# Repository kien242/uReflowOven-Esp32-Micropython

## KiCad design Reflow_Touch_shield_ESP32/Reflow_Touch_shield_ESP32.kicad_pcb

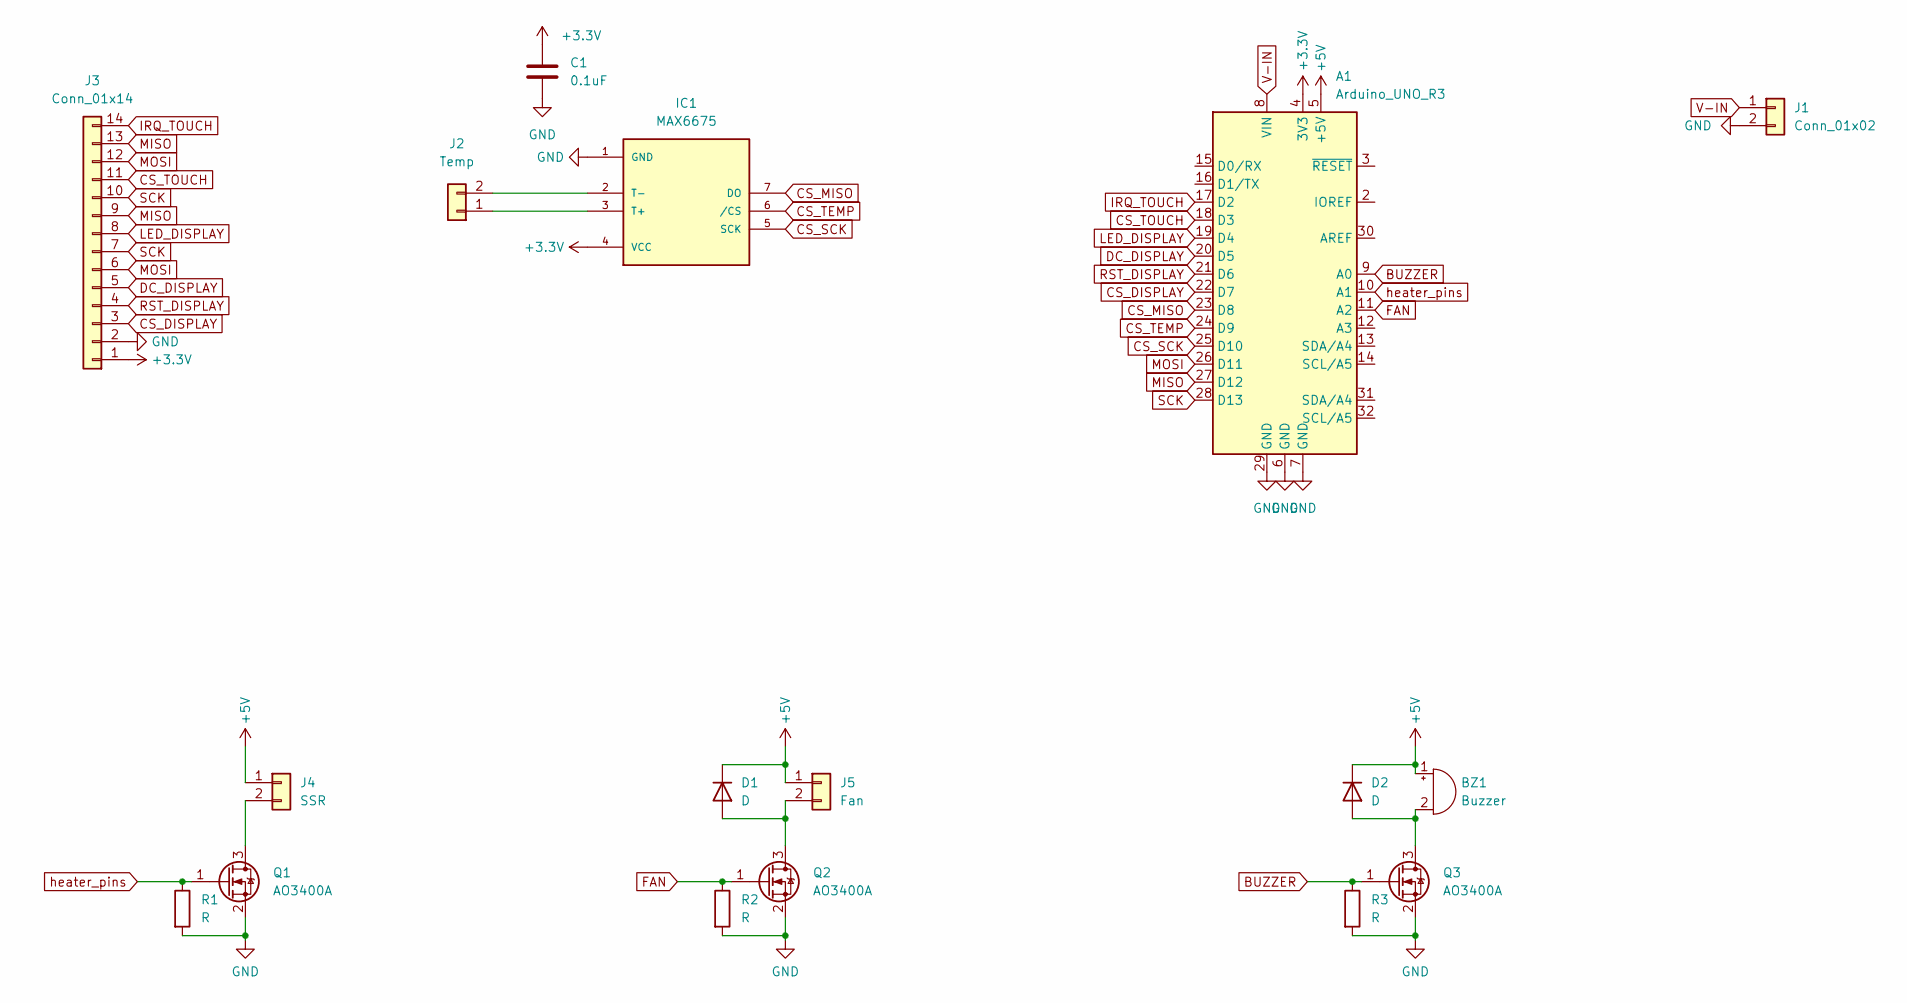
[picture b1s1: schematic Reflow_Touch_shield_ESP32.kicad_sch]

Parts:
A1: Arduino_UNO_R3
BZ1: Buzzer; MagneticBuzzer_CUI_CMT-8504-100-SMT
C1: 0.1uF; C_0603_1608Metric_Pad1.08x0.95mm_HandSolder
D1, D2: D; D_SOD-123
IC1: MAX6675; SO08
J1: Conn_01x02; TerminalBlock_Phoenix_MKDS-1,5-2-5.08_1x02_P5.08mm_Horizont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
J2: Temp; JST_EH_S2B-EH_1x02_P2.50mm_Horizontal
J3: Conn_01x14; ILI9341_PCB
J4: SSR; JST_EH_S2B-EH_1x02_P2.50mm_Horizontal
J5: Fan; JST_EH_S2B-EH_1x02_P2.50mm_Horizontal
Q1, Q2, Q3: AO3400A; SOT-23_Handsoldering
R1, R2, R3: R; R_0603_1608Metric_Pad0.98x0.95mm_HandSolder

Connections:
+3.3V: A1.4 (3V3), C1.1, IC1.4 (VCC), J3.1
+5V: A1.5 (+5V), BZ1.1 (-), D1.1 (K), D2.1 (K), J4.1, J5.1
BUZZER: A1.9 (A0), Q3.1 (G), R3.1
CS_DISPLAY: A1.22 (D7), J3.3
CS_MISO: A1.23 (D8), IC1.7 (DO)
CS_SCK: A1.25 (D10), IC1.5 (SCK)
CS_TEMP: A1.24 (D9), IC1.6 (/CS)
CS_TOUCH: A1.18 (D3), J3.11
DC_DISPLAY: A1.20 (D5), J3.5
FAN: A1.11 (A2), Q2.1 (G), R2.1
GND: A1.6 (GND), A1.7 (GND), A1.29 (GND), C1.2, IC1.1 (GND), J1.2, J3.2, Q1.2 (S), Q2.2 (S), Q3.2 (S), R1.2, R2.2, R3.2
IRQ_TOUCH: A1.17 (D2), J3.14
LED_DISPLAY: A1.19 (D4), J3.8
MISO: A1.27 (D12), J3.9, J3.13
MOSI: A1.26 (D11), J3.6, J3.12
unnamed: BZ1.2 (+), D2.2 (A), Q3.3 (D)
unnamed: D1.2 (A), J5.2, Q2.3 (D)
unnamed: IC1.2 (T-), J2.2
unnamed: IC1.3 (T+), J2.1
unnamed: J4.2, Q1.3 (D)
RST_DISPLAY: A1.21 (D6), J3.4
SCK: A1.28 (D13), J3.7, J3.10
V-IN: A1.8 (VIN), J1.1
heater_pins: A1.10 (A1), Q1.1 (G), R1.1

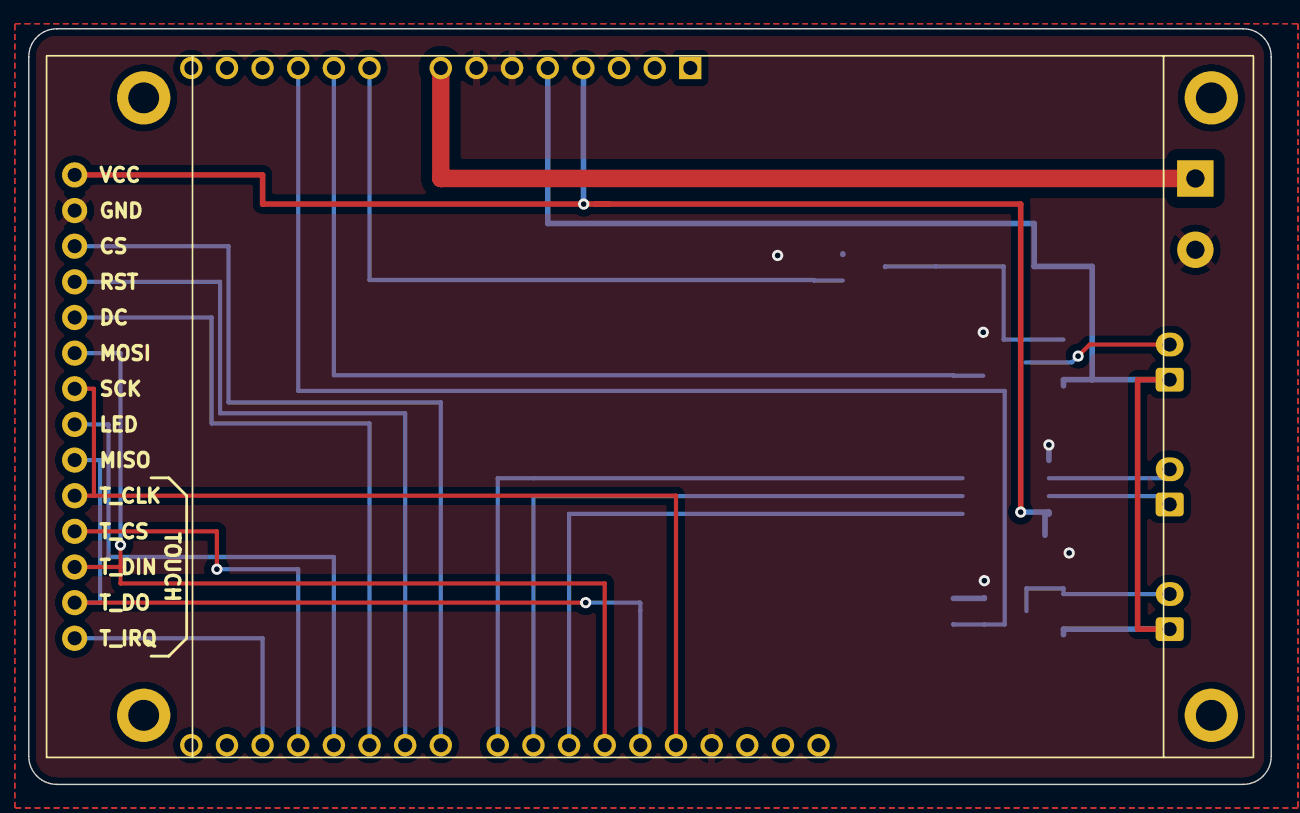
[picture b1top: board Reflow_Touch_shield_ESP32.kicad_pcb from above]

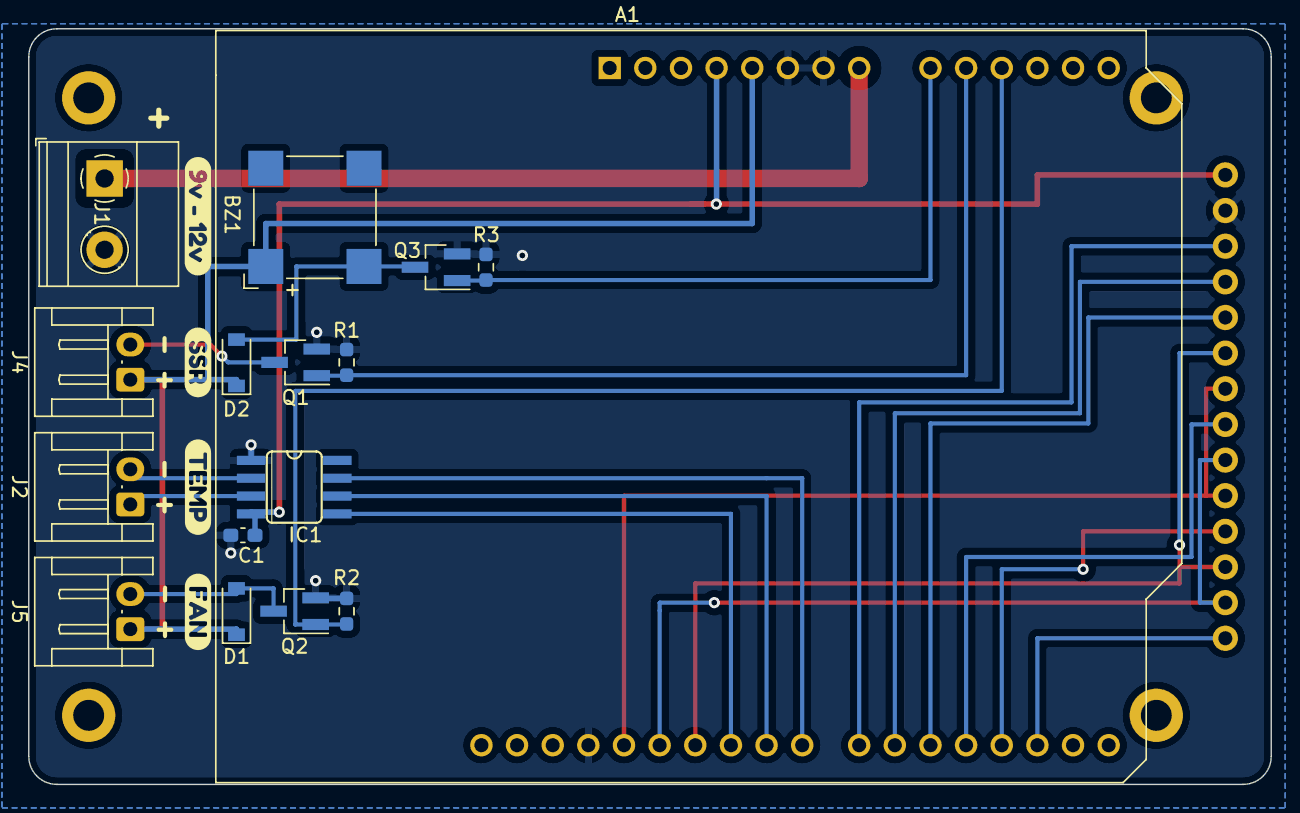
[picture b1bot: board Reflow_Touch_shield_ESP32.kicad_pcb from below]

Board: 2 copper layers, 88.5 x 53.8 mm, 21 parts (20 on the bottom side), 24 nets.

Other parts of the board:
kibuzzard-632DE3A2: G***; kibuzzard-632DE3A2
kibuzzard-632DE3CE: G***; kibuzzard-632DE3CE
kibuzzard-632DE383: G***; kibuzzard-632DE383
kibuzzard-632DE399: G***; kibuzzard-632DE399

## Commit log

2022-09-06 add PCB
2022-09-18 Update PCB
